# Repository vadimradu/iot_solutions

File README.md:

# iot_solutions
--
###Descriere
Repo-ul este impartit in trei parti:
* SIM_module, un shield pentru comunicare GSM
* WIFI_module, un shield pentru comunicare WIFI
* CTRL_module, un microcontroller pentru procesare

###Obiective
* Definirea unui format standard(optim pentru aplicatii portabile)
* Definirea unui header standart(unul pentru interfatare exterioara, unul pentru atasare usoara shielduri)
* Alegerea unor procesoare optime aplicatiei
* Completarea layouturilor

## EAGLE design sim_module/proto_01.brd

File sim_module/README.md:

Modul IoT cu sim-card
-----
###Descriere
 Modulul este construit in jurul unui [integrat de la SIMCOM][1] si este realizat intr-un format modular ce permite adaugarea lui intr-un sistem mai complex.

###Referinte
In folderul docs se gasesc doua documente de interes de la SIMCOM:
* [Design Reference](/docs/AN_SIM900 Reference Design Guide_V1.02.pdf)
* [PCB design](/docs/SIM900_Two-layer PCB RF Design_Application Note_V1.02.pdf)

Pe baza acestora trebuie realizat un layout de interfatare cu un modul host

###Obiective
  * Alegerea componentelor, vezi partea cu [BOM](README.md#BOM)
  * Completarea layoutului
    * Preferabil un singur strat
    * Numar mic de componente
    * Preferabil smd 0805 ca footprint pentru discrete
  * Respectarea conexiunilor pentru header
    * Standardul pentru header este inca in lucru
  * Footprinturi pentru componentele nonstandard

###Generalitati
  Nu prezinta interes partile de GPIO/PWM/I2C/DBG/LCD ...
  Trebuie doar conectat modulul SIM900A la un conector de SIM (preferabil microSIM)
  Trebuie conectate firele pentru comunicatii seriale (RXD, TXD) la un header

###BOM  
* Modul SIM900
* 2x Led 0805
* 2x Rez 0805
* Conector SIM, doua propuneri: [miniSIM][2] sau [microSIM][3]
* de completat...

  [1]: http://simcomm2m.com/En/module/detail.aspx?id=71
  [2]: http://ro.farnell.com/molex/78727-0001/connector-sim-socket-6pos/dp/2426393
  [3]: http://ro.farnell.com/multicomp/simmp-00601b000-g/connector-mini-sim-6pin/dp/2211802

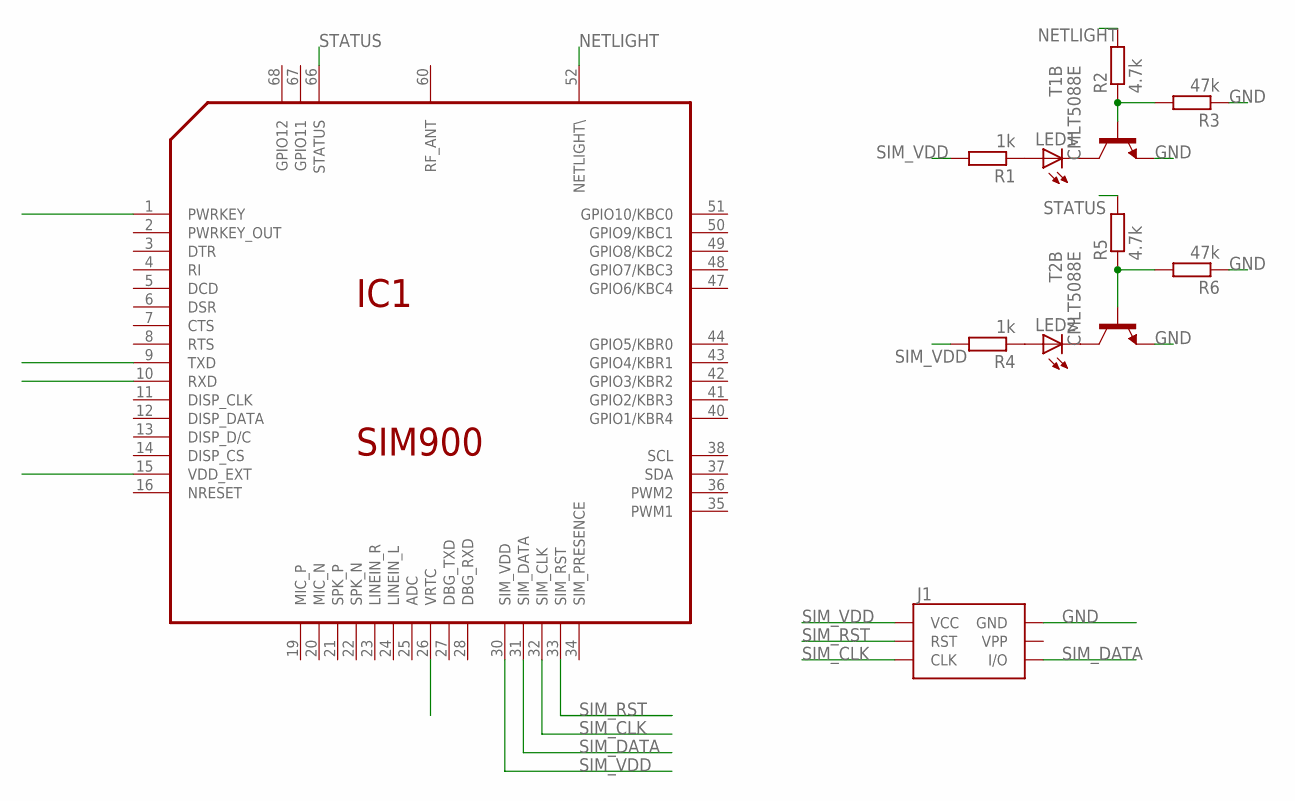
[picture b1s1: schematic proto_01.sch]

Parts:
IC1: SIM900
J1: SIMHOLDERSIM; SIMHOLDER
LED1, LED2: LED_ESML0603; LED_SML0603
R1, R4: 1k; R0805
R2, R5: 4.7k; R0805
R3, R6: 47k; R0805
T1, T2: CMLT5088E; SOT563

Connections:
GND: IC1.17 (GND), IC1.18 (GND), IC1.29 (GND), IC1.39 (GND), IC1.45 (GND), IC1.46 (GND), IC1.53 (GND), IC1.54 (GND), IC1.58 (GND), IC1.59 (GND), IC1.61 (GND), IC1.62 (GND), IC1.63 (GND), IC1.64 (GND), IC1.65 (GND), J1.C5 (GND), R3.1, R6.1, T1.4 (E), T2.4 (E)
unnamed: LED1.C, T1.3 (C)
unnamed: LED1.A, R1.1
unnamed: R2.1, R3.2, T1.5 (B)
unnamed: LED2.C, T2.3 (C)
unnamed: LED2.A, R4.1
unnamed: R5.1, R6.2, T2.5 (B)
NETLIGHT: IC1.52 (NETLIGHT\), R2.2
SIM_CLK: IC1.32 (SIM_CLK), J1.C3 (CLK)
SIM_DATA: IC1.31 (SIM_DATA), J1.C7 (I/O)
SIM_RST: IC1.33 (SIM_RST), J1.C2 (RST)
SIM_VDD: IC1.30 (SIM_VDD), J1.C1 (VCC), R1.2, R4.2
STATUS: IC1.66 (STATUS), R5.2
VBAT: IC1.55 (VBAT), IC1.56 (VBAT), IC1.57 (VBAT)

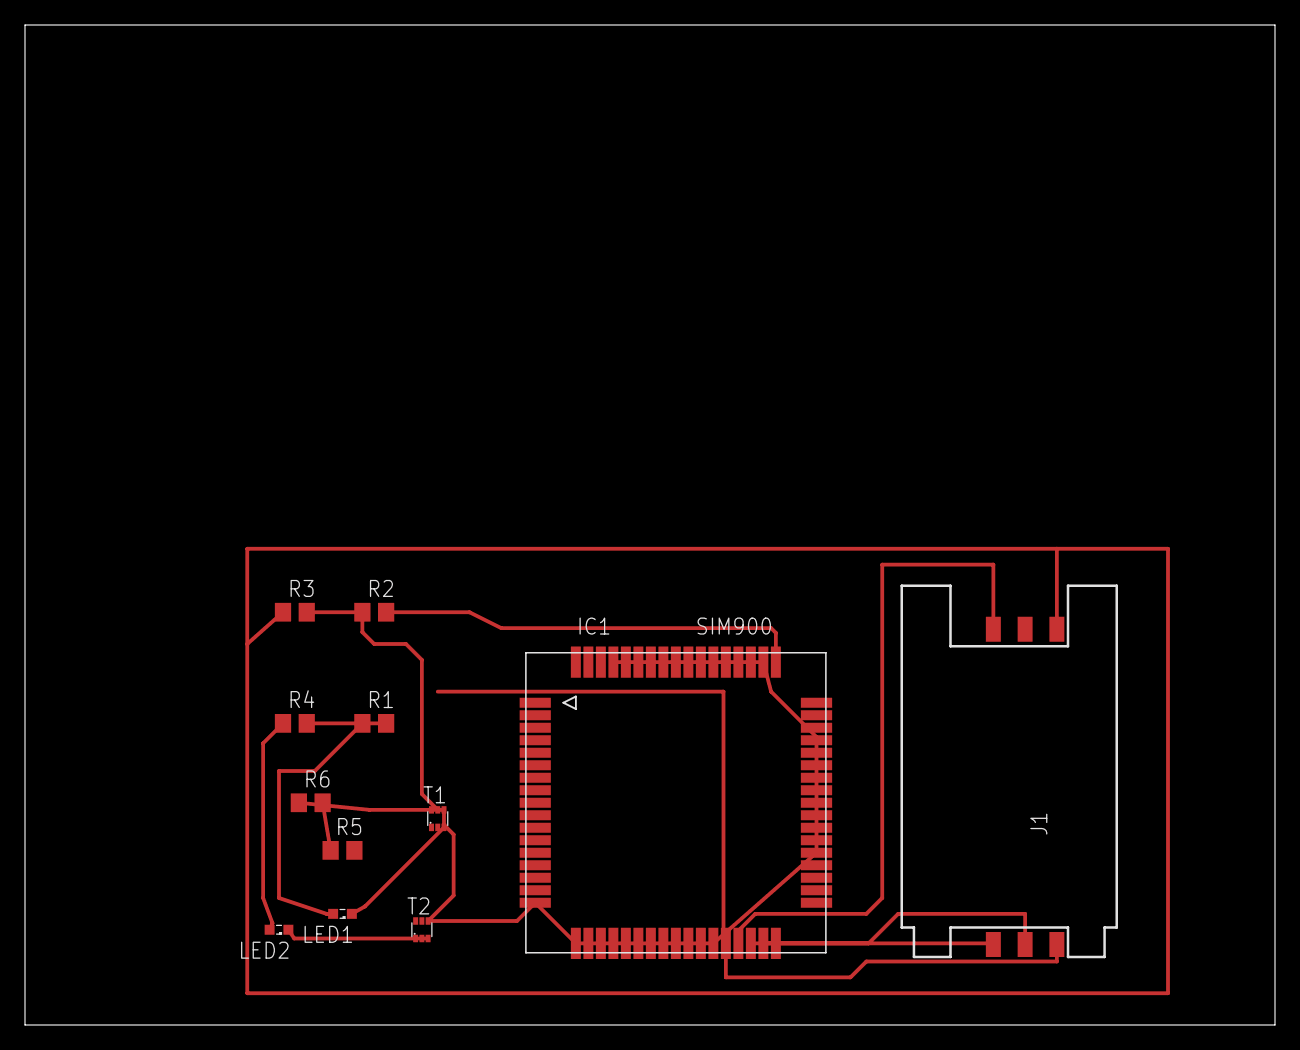
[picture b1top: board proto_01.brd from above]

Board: 2 copper layers, 100.0 x 80.0 mm, 12 parts (0 on the bottom side), 14 nets.

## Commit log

2015-07-21 :tada: Added .gitattributes & .gitignore files
2015-07-21 first upload
2015-07-23 Connected leds to status and netlight pins in schematics
    Connected leds to status and netlight pins in schematics
2015-07-24 Tried to do board for schematics
    Tried to do board for schematics
2015-08-15 added global library
2015-08-17 updated iot solution with minisim conector

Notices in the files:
parts and their libraries:
SparkFun-Connectors: Licensing: Creative Commons ShareAlike 4.0 International - https://creativecommons.org/licenses/by-sa/4.0
